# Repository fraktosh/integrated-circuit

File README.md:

# entire health platform for extensive wearable sensor data analytics and inference

```python
this entire project started with building a research project on developing local
federated models on health data on the basis of local regions to have sensitivity
or recall towards anomalies. but a device such that doesn't exist that's viable to
do a large scale study on people, so we created the device, FROM SCRATCH.
this project is something that came out of my heart, and everything we developed
is with LOVE, so please support and contribute if you can.

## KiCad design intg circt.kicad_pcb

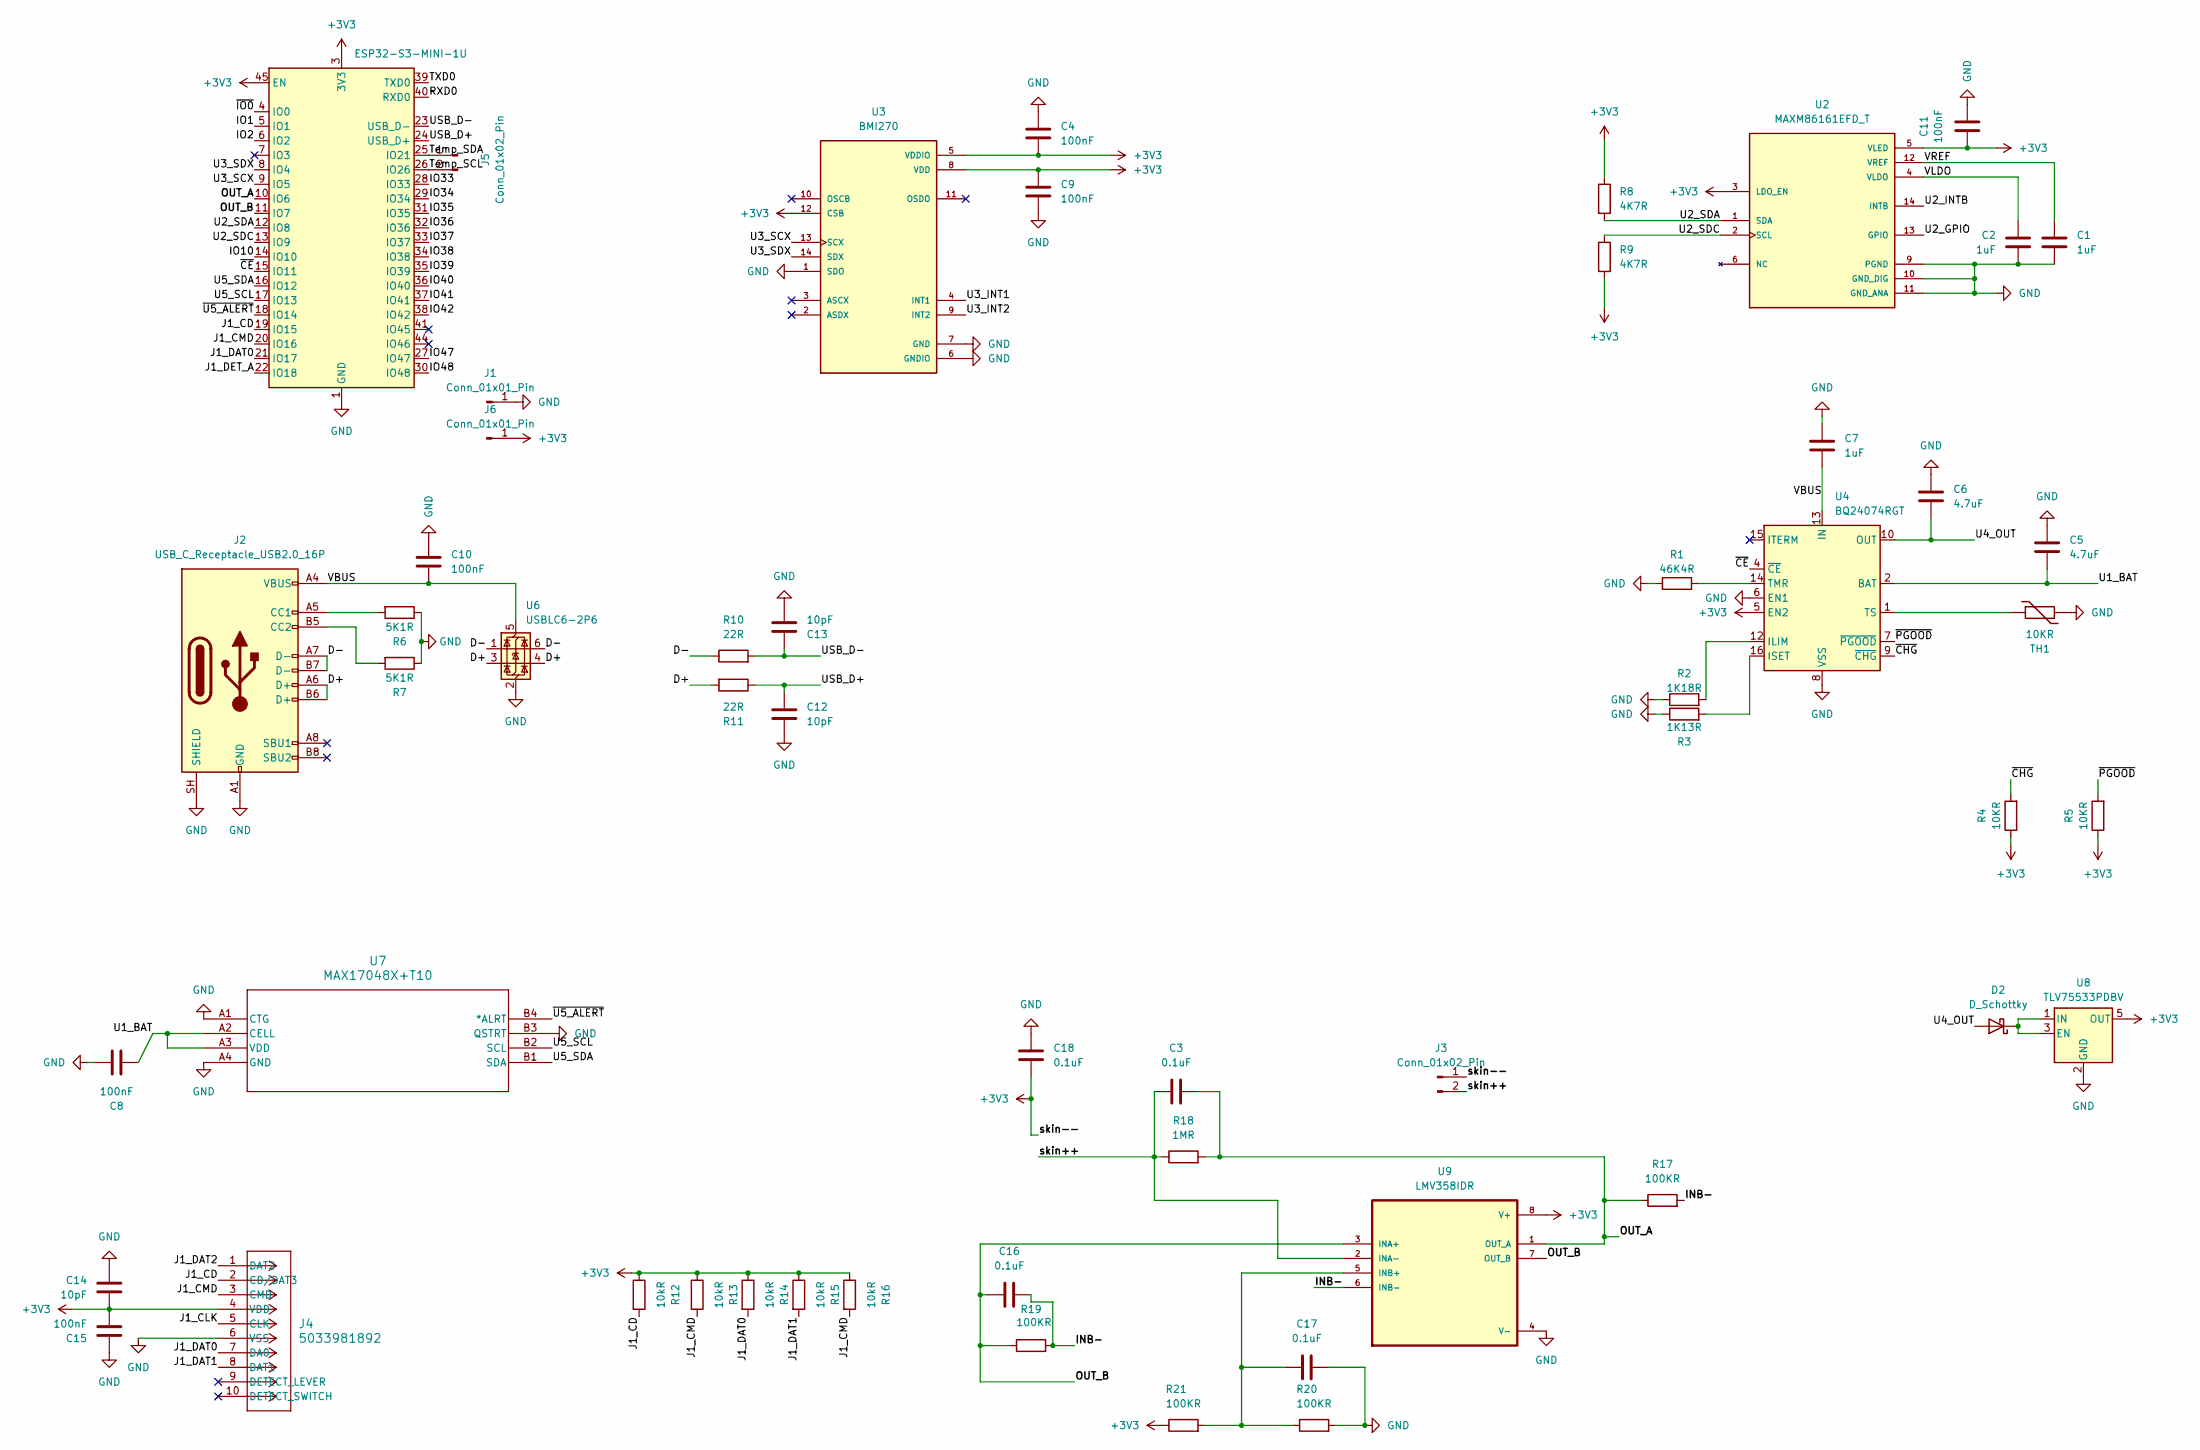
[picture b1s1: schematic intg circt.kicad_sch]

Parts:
C1, C2, C7: 1uF; C_0201_0603Metric
C3, C16, C17, C18: 0.1uF; C_0201_0603Metric
C4, C8, C9, C10, C11, C15: 100nF; C_0201_0603Metric
C5, C6: 4.7uF; C_0201_0603Metric
C12, C13, C14: 10pF; C_0201_0603Metric
D2: D_Schottky; D_0201_0603Metric
J1, J6: Conn_01x01_Pin; PinHeader_1x01_P1.00mm_Vertical
J2: USB_C_Receptacle_USB2.0_16P; USB_C_Receptacle_GCT_USB4105-xx-A_16P_TopMnt_Horizontal
J3, J5: Conn_01x02_Pin; PinHeader_1x02_P1.00mm_Vertical
J4: 5033981892; CONN_503398-1892_MOL
R1: 46K4R; R_0201_0603Metric
R2: 1K18R; R_0201_0603Metric
R3: 1K13R; R_0201_0603Metric
R4, R5: 10KR; R_0201_0603Metric
R6, R7: 5K1R; R_0201_0603Metric
R8, R9: 4K7R; R_0201_0603Metric
R10, R11: 22R; R_0201_0603Metric
R12, R13, R14, R15, R16: 10kR; R_0201_0603Metric
R17, R19, R20, R21: 100KR; R_0201_0603Metric
R18: 1MR; R_0201_0603Metric
TH1: 10KR; R_0201_0603Metric
U1: ESP32-S3-MINI-1U; ESP32-S2-MINI-1U
U2: MAXM86161EFD_T; PSON60P430X290X150-14N; PARTREV 1
U3: BMI270; XDCR_BMI270
U4: BQ24074RGT; VQFN-16-1EP_3x3mm_P0.5mm_EP1.6x1.6mm
U6: USBLC6-2P6; SOT-666
U7: MAX17048X+T10; 21-0555B_W80B1-1_MXM
U8: TLV75533PDBV; SOT-23-5
U9: LMV358IDR

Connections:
+3V3: C4.2, C9.2, C11.1, C14.1, C15.1, C18.1, J3.1, J4.4 (VDD), J6.1 (Pin_1_1), R4.1, R5.1, R8.1, R9.2, R12.1, R13.1, R14.1, R15.1, R16.1, R21.1, U1.3 (3V3), U1.45 (EN), U2.3 (LDO_EN), U2.5 (VLED), U3.5 (VDDIO), U3.8 (VDD), U3.12 (CSB), U4.5 (EN2), U8.5 (OUT), U9.8 (V+)
/D+: J2.A6 (D+), J2.B6 (D+), R11.2, U6.3 (I/O2), U6.4 (I/O2)
/D-: J2.A7 (D-), J2.B7 (D-), R10.1, U6.1 (I/O1), U6.6 (I/O1)
/INB-: C16.2, R17.2, R19.2, U9.6 (INB-)
/IO1: U1.5 (IO1)
/IO2: U1.6 (IO2)
/IO10: U1.14 (IO10)
/IO33: U1.28 (IO33)
/IO34: U1.29 (IO34)
/IO35: U1.31 (IO35)
/IO36: U1.32 (IO36)
/IO37: U1.33 (IO37)
/IO38: U1.34 (IO38)
/IO39: U1.35 (IO39)
/IO40: U1.36 (IO40)
/IO41: U1.37 (IO41)
/IO42: U1.38 (IO42)
/IO47: U1.27 (IO47)
/IO48: U1.30 (IO48)
/J1_CD: J4.2 (CD/DAT3), R12.2, U1.19 (IO15)
/J1_CLK: J4.5 (CLK)
/J1_CMD: J4.3 (CMD), R13.2, R16.2, U1.20 (IO16)
/J1_DAT0: J4.7 (DA0), R14.2, U1.21 (IO17)
/J1_DAT1: J4.8 (DAT1), R15.2
/J1_DAT2: J4.1 (DAT2)
/J1_DET_A: U1.22 (IO18)
/OUT_A: C3.2, R17.1, R18.2, U1.10 (IO6), U9.1 (OUT_A)
/OUT_B: C16.1, R19.1, U1.11 (IO7), U9.3 (INA+), U9.7 (OUT_B)
/RXD0: U1.40 (RXD0)
/TXD0: U1.39 (TXD0)
/Temp_SCL: J5.2, U1.26 (IO26)
/Temp_SDA: J5.1, U1.25 (IO21)
/U1_BAT: C5.2, C8.1, U4.2 (BAT), U4.3 (BAT), U7.A2 (CELL), U7.A3 (VDD)
/U2_GPIO: U2.13 (GPIO)
/U2_INTB: U2.14 (INTB)
/U2_SDA: R8.2, U1.12 (IO8), U2.1 (SDA)
/U2_SDC: R9.1, U1.13 (IO9), U2.2 (SCL)
/U3_INT1: U3.4 (INT1)
/U3_INT2: U3.9 (INT2)
/U3_SCX: U1.9 (IO5), U3.13 (SCX)
/U3_SDX: U1.8 (IO4), U3.14 (SDX)
/U4_OUT: C6.2, D2.2 (A), U4.10 (OUT), U4.11 (OUT)
/U5_SCL: U1.17 (IO13), U7.B2 (SCL)
/U5_SDA: U1.16 (IO12), U7.B1 (SDA)
/USB_D+: C12.2, R11.1, U1.24 (USB_D+)
/USB_D-: C13.2, R10.2, U1.23 (USB_D-)
/VBUS: C7.2, C10.1, J2.A4 (VBUS), J2.A9 (VBUS), J2.B4 (VBUS), J2.B9 (VBUS), U4.13 (IN), U6.5 (VBUS)
/VLDO: C2.1, U2.4 (VLDO)
/VREF: C1.1, U2.12 (VREF)
/skin++: C3.1, J3.2, R18.1, U9.2 (INA-)
/~CE: U1.15 (IO11), U4.4 (~CE)
/~CHG: R4.2, U4.9 (~CHG)
/~IO0: U1.4 (IO0)
/~PGOOD: R5.2, U4.7 (~PGOOD)
/~U5_ALERT: U1.18 (IO14), U7.B4 (*ALRT)
GND: C1.2, C2.2, C4.1, C5.1, C6.1, C7.1, C8.2, C9.1, C10.2, C11.2, C12.1, C13.1, C14.2, C15.2, C17.2, C18.2, J1.1 (Pin_1_1), J2.A1 (GND), J2.A12 (GND), J2.B1 (GND), J2.B12 (GND), J2.SH (SHIELD), J4.6 (VSS), R1.1, R2.1, R3.1, R6.1, R7.1, R20.2, TH1.2, U1.1 (GND), U1.2 (GND), U1.42 (GND), U1.43 (GND), U1.46 (GND), U1.47 (GND), U1.48 (GND), U1.49 (GND), U1.50 (GND), U1.51 (GND), U1.52 (GND), U1.53 (GND), U1.54 (GND), U1.55 (GND), U1.56 (GND), U1.57 (GND), U1.58 (GND), U1.59 (GND), U1.60 (GND), U1.61 (GND), U1.62 (GND), U1.63 (GND), U1.64 (GND), U1.65 (GND), U2.9 (PGND), U2.10 (GND_DIG), U2.11 (GND_ANA), U3.1 (SDO), U3.6 (GNDIO), U3.7 (GND), U4.6 (EN1), U4.8 (VSS), U4.17 (VSS), U6.2 (GND), U7.A1 (CTG), U7.A4 (GND), U7.B3 (QSTRT), U8.2 (GND), U9.4 (V-)
unnamed: D2.1 (K), U8.1 (IN), U8.3 (EN)
unnamed: J2.A5 (CC1), R6.2
unnamed: J2.B5 (CC2), R7.2
unnamed: R2.2, U4.12 (ILIM)
unnamed: R3.2, U4.16 (ISET)
unnamed: R1.2, U4.14 (TMR)
unnamed: TH1.1, U4.1 (TS)
unnamed: C17.1, R20.1, R21.2, U9.5 (INB+)

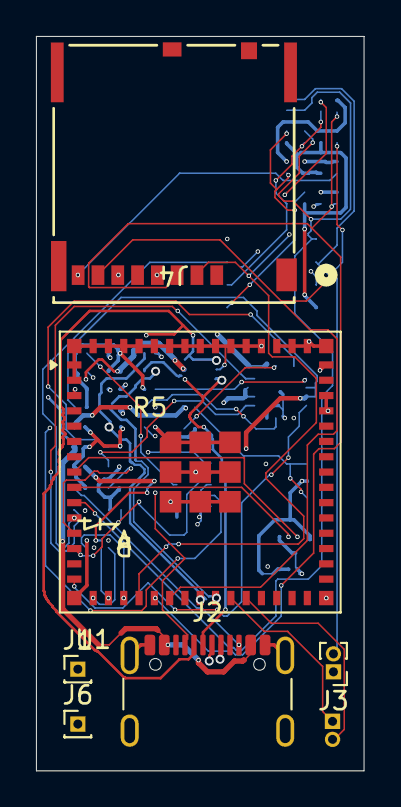
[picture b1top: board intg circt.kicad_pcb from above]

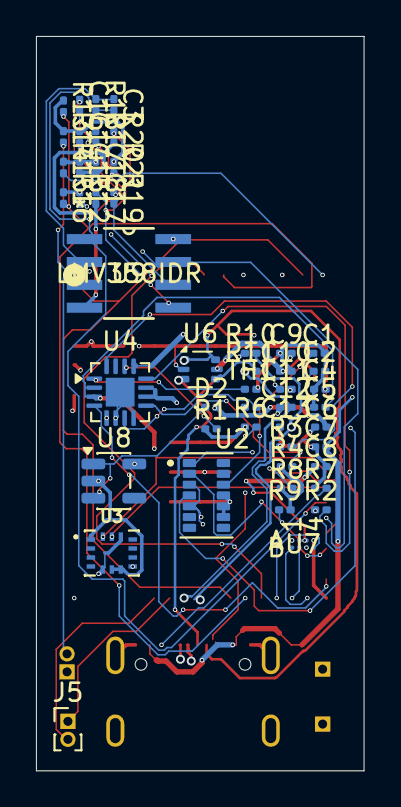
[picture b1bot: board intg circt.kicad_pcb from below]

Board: 4 copper layers, 18.2 x 40.8 mm, 55 parts (49 on the bottom side), 39 nets.

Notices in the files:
parts and their libraries:
Copyright 2016 Accelerated Designs. All rights reserved.
